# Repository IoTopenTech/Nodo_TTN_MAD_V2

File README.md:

# Nodo_TTN_MAD_V2_2
Documentación, hardware y software del nodo TTN MAD V2.2 desarrollado por la comunidad The Things Network Madrid
En el wiki de este repositorio encontrarás más información sobre cómo montar/adquirir este nodo.
Si lo deseas, también puedes adquirirlo como un kit para montar o ya montado directamente en España (con factura) a través de Molukas:
https://shop.molukas.com/es/inicio/19-56-nodo-ttn-mad-v22.html#/23-terminacion-ensamblado_y_con_bootloader_preinstalado

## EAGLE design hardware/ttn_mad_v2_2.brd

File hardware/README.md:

Archivos en formato Eagle y PDF.

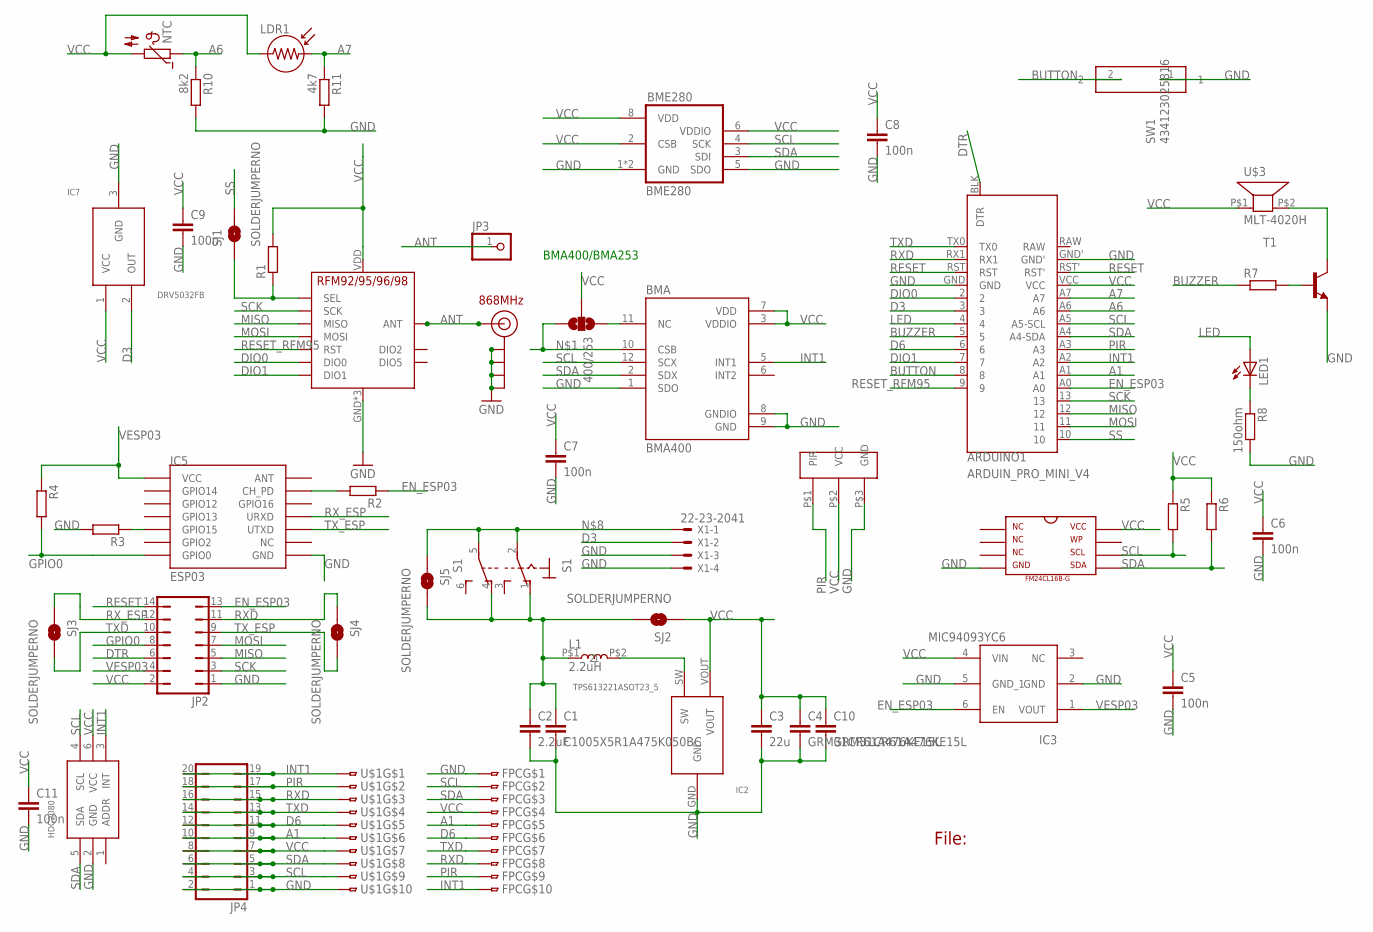
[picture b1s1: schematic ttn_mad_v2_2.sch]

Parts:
400/253: SOLDERJUMPER_2WAYT; SJ_2
ARDUINO1: ARDUIN_PRO_MINI_V4; ARDUINO_PRO_MINI_V4
BMA: BMA400; IC_BMA400
BME280: BME280
C1: C1005X5R1A475K050BC; C0603
C2: 2.2uF; C0603
C3: 22u; C0805
C4, C10: GRM31CR61A476KE15L; C0805
C5, C6, C7, C8, C9, C11: 100n; C0603
FM24: FM24CL16B-G
FPC: FPC_10P_0_5MM; FH12-10S-0.5SH
HDC2080: HDC2080; WSON-6
IC2: TPS613221ASOT23_5; SOT23-5L
IC3: MIC94093YC6; SC70-6
IC5: ESP03
IC7: DRV5032FB; SOT23
J$2: ANTENNATINY; SMA_UFL_PAD_TINY
JP2: JP7Q
JP3: PINHD-1X1; 1X01
JP4: JP10Q
L1: 2.2uH; SRN2512
LDR1: LDR
LED1: LEDSMT1206; 1206
NTC: NTC640; P640
R1, R2, R3, R4, R5, R6, R7: R-EU_R0603; R0603
R8: 150ohm; R0603
R10: 8k2; R0603
R11: 4k7; R0603
S1: TOGGLE_SWITCHTS_SMD; TOGGLE_SWITCH_SMD
SJ1, SJ2, SJ3, SJ4, SJ5: SOLDERJUMPERNO; SJ_2S-NO
SW1: 434123025816
T1: BC817-16-NPN-SOT23-BEC; SOT23-BEC
U$1: FPC_10P_0_5MM; FH12-10S-0.5SH
U$3: MLT-4020H
U$5: RFM95
U$6: PIR
X1: 22-23-2041

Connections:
A1: ARDUINO1.A1, FPC.5, JP4.9, JP4.10, U$1.6
A6: ARDUINO1.A6, NTC.1, R10.1
A7: ARDUINO1.A7, LDR1.2, R11.1
ANT: J$2.ANT1 (SIGNAL), J$2.ANT2 (SIGNAL), J$2.ANT3 (SIGNAL), JP3.1, U$5.ANT
BUTTON: ARDUINO1.8, SW1.2
BUZZER: ARDUINO1.5, R7.1
D3: ARDUINO1.3, IC7.2 (OUT), X1.2
D6: ARDUINO1.6, FPC.6, JP4.11, JP4.12, U$1.5
DIO0: ARDUINO1.2, U$5.DIO0
DIO1: ARDUINO1.7, U$5.DIO1
DTR: ARDUINO1.BLK (DTR), JP2.6
EN_ESP03: ARDUINO1.A0, IC3.6 (EN), JP2.13, R2.1
GND: ARDUINO1.GND, ARDUINO1.GND', BMA.1 (SDO), BMA.8 (GNDIO), BMA.9 (GND), BME280.1 (GND), BME280.5 (SDO), BME280.7 (GND), C1.2, C2.2, C3.2, C4.2, C5.2, C6.2, C7.2, C8.2, C9.2, C10.2, C11.2, FM24.4, FPC.1, HDC2080.2 (GND), IC2.GND, IC3.2 (GND), IC3.5 (GND_1), IC5.GND, IC7.3 (GND), J$2.GND1 (GND), J$2.GND2 (GND), J$2.GND3 (GND), J$2.GND4 (GND), JP2.1, JP4.1, JP4.2, R3.2, R8.2, R10.2, R11.2, SW1.1, T1.E, U$1.10, U$5.GND, U$5.GND1 (GND), U$5.GND2 (GND), U$6.P$3 (GND), X1.3, X1.4
GPIO0: IC5.GPIO0, JP2.8, R4.2
INT1: ARDUINO1.A2, BMA.5 (INT1), FPC.10, HDC2080.3 (INT), JP4.19, JP4.20, U$1.1
LED: ARDUINO1.4, LED1.A
MISO: ARDUINO1.12, JP2.5, U$5.MISO
MOSI: ARDUINO1.11, JP2.7, U$5.MOSI
unnamed: 400/253.3, BMA.10 (CSB)
unnamed: R1.1, SJ1.1, U$5.NSS (SEL)
unnamed: IC2.SW, L1.P$2 (2)
unnamed: IC5.GPIO15, R3.1
unnamed: T1.C, U$3.P$2 (2)
unnamed: 400/253.1, BMA.11 (NC)
unnamed: R7.2, T1.B
unnamed: S1.2, S1.5, SJ5.1, X1.1
unnamed: LED1.C, R8.1
unnamed: IC5.CH_PD, R2.2
PIR: ARDUINO1.A3, FPC.9, JP4.17, JP4.18, U$1.2, U$6.P$1 (PIR)
RESET: ARDUINO1.RST, ARDUINO1.RST', JP2.14
RESET_RFM95: ARDUINO1.9, U$5.RST
RXD: ARDUINO1.RX1, FPC.8, JP2.11, JP4.15, JP4.16, SJ4.1, U$1.3
RX_ESP: IC5.URXD, JP2.12, SJ3.1
SCK: ARDUINO1.13, JP2.3, U$5.SCK
SCL: ARDUINO1.A5 (A5-SCL), BMA.12 (SCX), BME280.4 (SCK), FM24.6, FPC.2, HDC2080.4 (SCL), JP4.3, JP4.4, R5.2, U$1.9
SDA: ARDUINO1.A4 (A4-SDA), BMA.2 (SDX), BME280.3 (SDI), FM24.5, FPC.3, HDC2080.5 (SDA), JP4.5, JP4.6, R6.2, U$1.8
SS: ARDUINO1.10, SJ1.2
TXD: ARDUINO1.TX0, FPC.7, JP2.10, JP4.13, JP4.14, SJ3.2, U$1.4
TX_ESP: IC5.UTXD, JP2.9, SJ4.2
VCC: 400/253.2, ARDUINO1.VCC, BMA.3 (VDDIO), BMA.7 (VDD), BME280.2 (CSB), BME280.6 (VDDIO), BME280.8 (VDD), C3.1, C4.1, C5.1, C6.1, C7.1, C8.1, C9.1, C10.1, C11.1, FM24.8, FPC.4, HDC2080.6 (VCC), IC2.VOUT, IC3.4 (VIN), IC7.1 (VCC), JP2.2, JP4.7, JP4.8, LDR1.1, NTC.2, R1.2, R5.1, R6.1, SJ2.1, U$1.7, U$3.P$1 (1), U$5.VDD (VCC), U$6.P$2 (VCC)
VCC_BAT: C1.1, C2.1, L1.P$1 (1), S1.1 (O), S1.4 (O), SJ2.2, SJ5.2
VESP03: IC3.1 (VOUT), IC5.VCC, JP2.4, R4.1

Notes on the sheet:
File:
868MHz
BMA400/BMA253

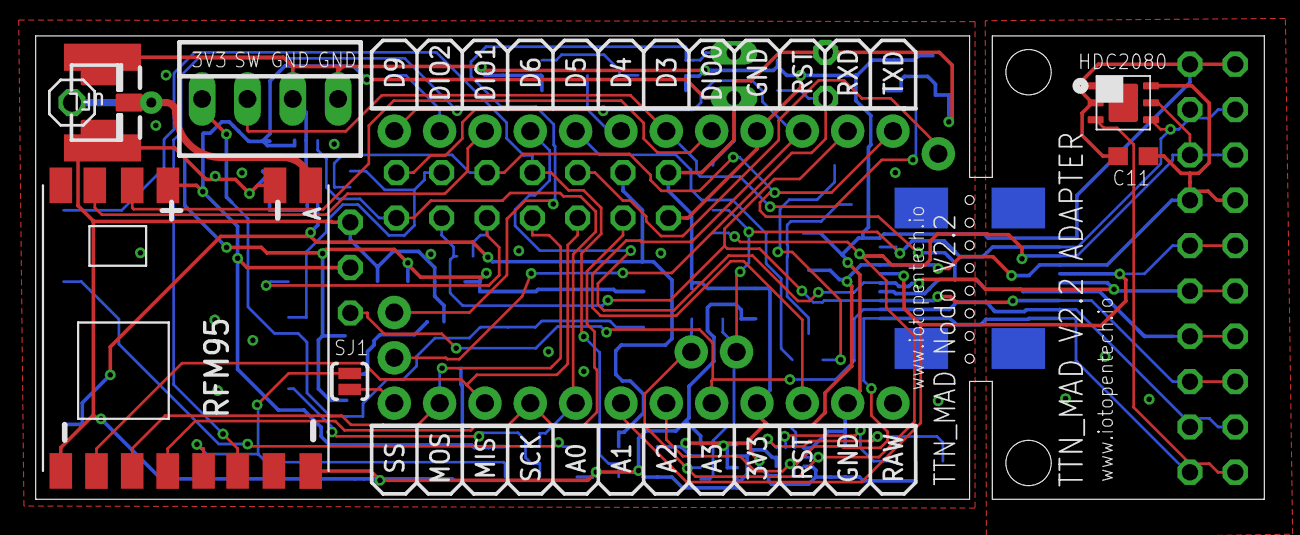
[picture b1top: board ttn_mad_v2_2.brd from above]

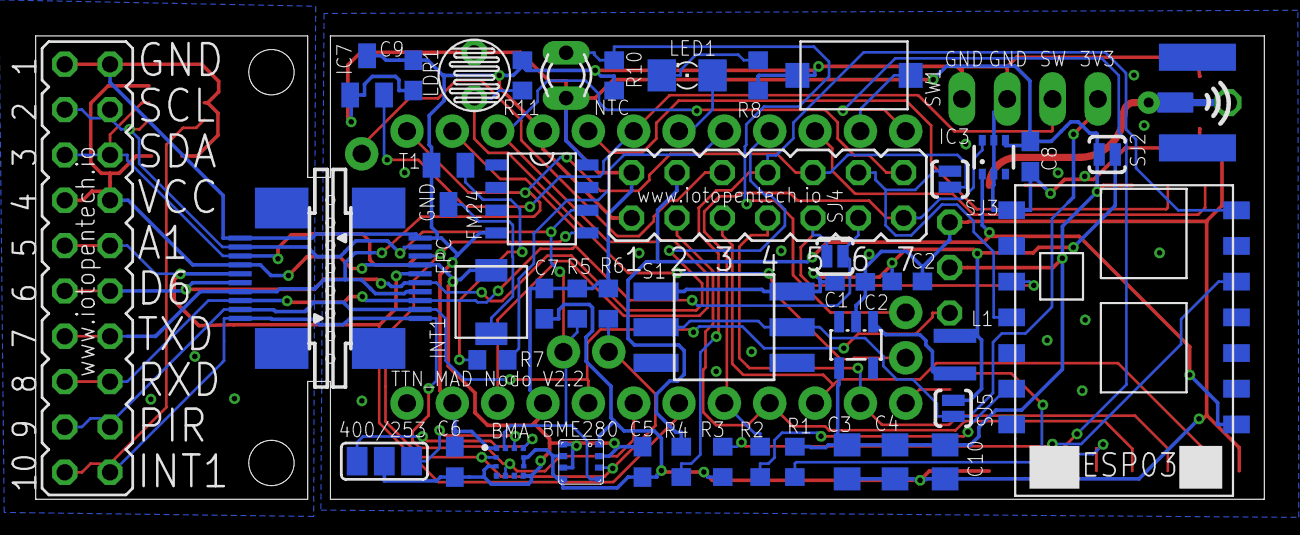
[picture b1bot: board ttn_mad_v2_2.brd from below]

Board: 2 copper layers, 68.8 x 26.0 mm, 53 parts (45 on the bottom side), 42 nets.

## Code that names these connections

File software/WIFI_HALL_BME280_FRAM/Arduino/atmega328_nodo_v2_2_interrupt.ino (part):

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  pinMode(3, INPUT_PULLUP);//SENSOR PUERTA
  pinMode(8, INPUT_PULLUP);//BOTON
  pinMode(4, OUTPUT);//LED
  pinMode(5, OUTPUT);//BUZZER
  pinMode(6, INPUT);//External
  pinMode(A0, OUTPUT);//EN_ESP03
  digitalWrite(A0, LOW);
  pinMode(A1, INPUT);//EXTERNAL
  pinMode(A2, INPUT);//INT1
  pinMode(A3, INPUT);//PIR

  //Wire.begin();

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
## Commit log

2019-09-26 Rename readme.md to README.md
2020-01-16 Reconfiguración de directorios
2020-01-26 Donde esta mi mochila
2020-01-26 Correccion imagen
2020-01-26 correccion readme
2020-02-12 ttnmapper single channel
2020-02-16 Ejemplos con downlink al LED

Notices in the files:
parts and their libraries:
SparkFun-Passives: Licensing: Creative Commons ShareAlike 4.0 International - https://creativecommons.org/licenses/by-sa/4.0
Eagle_Wuerth_Elektronik_Switch: Copyright: Würth Elektronik
